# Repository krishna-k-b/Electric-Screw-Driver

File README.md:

# Electric-Screw-Driver
Attempt to make a Torque-sensing DC screwdriver using motor current feedback for real-time torque estimation and inertia aware control

# DRV8701 + RP2040 Brushed DC Screwdriver

Firmware for a handheld brushed-DC screwdriver using a Raspberry Pi Pico (RP2040) and a DRV8701 gate driver in PH/EN mode with an external N-MOSFET H-bridge. Features closed-loop current sensing, configurable torque limiting, soft-start, dithering, and full serial telemetry over CMSIS-DAP / Picoprobe.

## Table of Contents

- [Hardware Overview](#hardware-overview)
- [Pin Map](#pin-map)
- [Current Sensing Circuit](#current-sensing-circuit)
- [Building](#building)
- [Flashing](#flashing)
- [Debug / Serial Interface](#debug--serial-interface)
- [Serial Commands](#serial-commands)
- [State Machine](#state-machine)
- [Torque Control](#torque-control)
- [LED Indicator](#led-indicator)
- [Configuration Reference](#configuration-reference)

---

## Hardware Overview

| Component | Part |
|---|---|
| MCU | Raspberry Pi Pico (RP2040) |
| Gate driver | Texas Instruments DRV8701 |
| Bridge topology | External N-MOSFET H-bridge (PH/EN mode) |
| Current sense | 5 mΩ shunt + DRV8701 SO pin + resistor divider |
| Trigger | Two momentary buttons — CW (GP13) and CCW (GP12) |
| Speed control | Fixed 100 % duty with soft-start ramp (no pot fitted) |

---

## Pin Map

| GPIO | Direction | Function |
|---|---|---|
| GP0 | OUT | UART0 TX → Picoprobe GP5 |
| GP1 | IN | UART0 RX → Picoprobe GP4 |
| GP12 | IN (pull-up) | Button CCW — active LOW |
| GP13 | IN (pull-up) | Button CW — active LOW |
| GP16 | OUT (PWM) | DRV8701 EN/PWM — 20 kHz |
| GP17 | OUT | DRV8701 PH/DIR — HIGH = CW |
| GP18 | OUT | DRV8701 nSLEEP — LOW = Hi-Z |
| GP19 | IN (pull-up) | DRV8701 nFAULT — open-drain active LOW |
| GP26 | AIN | ADC CH0 — SO current sense |
| GP27 | AIN | ADC CH1 — pot (wired, reading disabled) |
| GP25 | OUT | Onboard LED |

---

## Current Sensing Circuit

The DRV8701 SO pin outputs a voltage proportional to motor current. A resistor divider scales it to the RP2040's 3.3 V ADC range.

```
SO pin ──┬── 10 kΩ ──── 3.3 V
         │
         ├── GP26 (ADC CH0)
         │
        20 kΩ
         │
        GND
```

| Parameter | Value |
|---|---|
| Divider ratio (V_ADC / V_SO) | 0.6667 (20 / 30) |
| Amplifier gain | 20 V/V |
| Sense resistor | 5 mΩ |
| SO offset voltage | 50 mV |

**Current calculation** (per loop tick):

```
V_SO_real      = V_ADC / 0.6667
V_SO_on_phase  = V_SO_real / duty_fraction      ← duty-cycle compensation
V_across_amp   = V_SO_on_phase − 0.050 V
I              = V_across_amp / (20 × 0.005)
```

Readings are frozen when duty < 10 % to avoid noise during near-zero on-time. A first-order IIR filter (α = 0.25) smooths the result.

---

## Building

### Prerequisites

- [Raspberry Pi Pico SDK](https://github.com/raspberrypi/pico-sdk) (≥ 1.5)
- CMake ≥ 3.13
- `arm-none-eabi-gcc`

### CMakeLists.txt fragment

```cmake
add_executable(screwdriver DRV_ESD.cpp)

target_link_libraries(screwdriver PRIVATE
    pico_stdlib
    hardware_pwm
    hardware_adc
    hardware_gpio
    hardware_uart
    hardware_watchdog
    hardware_clocks
)

pico_enable_stdio_uart(screwdriver 1)
pico_enable_stdio_usb(screwdriver 0)
pico_add_extra_outputs(screwdriver)
```

### Build

```bash
mkdir build && cd build
cmake ..
make -j4
```

This produces `DRV_ESD.uf2`.

---

## Flashing

Hold the **BOOTSEL** button on the Pico while plugging in USB. Drag `DRV_ESD.uf2` onto the `RPI-RP2` mass-storage device that appears. The board resets and starts running immediately.
Above is for flashing without debugger, i usually flash the .elf file through debugger. Read Pico Debug documentation should you wish to flash using a debugger.

---

## Debug / Serial Interface

Connect a second Pico running [Picoprobe](https://github.com/raspberrypi/picoprobe) firmware:

| Target | Picoprobe |
|---|---|
| GP0 (TX) | GP5 |
| GP1 (RX) | GP4 |
| GND | GND |

Open the CDC serial port at **921 600 baud, 8N1**. All log lines are prefixed with a millisecond timestamp:

```
[T+   1234 ms] STATE  IDLE -> STARTING  [trigger engaged]
[T+   1284 ms] TELEM  STARTING  dir=CW   I= 0.12A ...
```

---

## Serial Commands

Send commands surrounded by angle brackets, e.g. `<help>`.

| Command | Description |
|---|---|
| `<help>` | Full status dump + command list |
| `<status>` | Same as `<help>` |
| `<cw>` | Start motor CW (latched until `<stop>` or torque trip) |
| `<ccw>` | Start motor CCW (latched until `<stop>` or torque trip) |
| `<stop>` | Clear any serial motor request |
| `<ith X.X>` | Set current threshold in amps, e.g. `<ith 4.5>` |

Serial requests behave identically to physical button presses. `<cw>` and `<ccw>` are only accepted from **IDLE** or **STOPPED**; they are ignored and logged otherwise.

---

## State Machine

```
         ┌──────────────────────────────────────────────────────────────────┐
         │  nFAULT asserted (any time)                                      ▼
  BOOT ──► IDLE ──trigger──► STARTING ──ramp done──► RUNNING               FAULT
           ▲                    │                      │  │                   │
           │              early release             trip │  I > 80% Ith       │ nFAULT clear
           │                    │                        ▼  ▼              + holdoff
           │                    └───────────────► STOPPING ◄── DITHERING      │
           │                                          │             │          │
           │                                    cooldown done       │ I < 60% Ith
           │                                          ▼             │
           └──────────────── trigger released ── STOPPED            └──► RUNNING
```

| State | Description |
|---|---|
| `BOOT` | One-shot init, transitions immediately to `IDLE` |
| `IDLE` | Waiting for trigger; bridge is in sleep / Hi-Z |
| `STARTING` | 200 ms linear duty ramp from 0 → 100 % |
| `RUNNING` | Full duty, monitoring current |
| `DITHERING` | Near threshold — duty modulated to hold current just below limit |
| `STOPPING` | EN = 0 (brake), 300 ms cooldown before sleep |
| `STOPPED` | Bridge asleep; waiting for trigger release before next run |
| `FAULT` | nFAULT asserted by DRV8701; motor braked, LED solid ON |

**Trigger logic** — either the physical button *or* a latched serial request counts as a trigger. If both CW and CCW are simultaneously active (buttons or serial), no motion occurs until the conflict resolves.

---

## Torque Control

Three layered mechanisms protect the motor and workpiece:

### 1. Threshold current trip (sustained overcurrent)

The firmware trips if `I_filtered ≥ I_threshold` persists for **5 consecutive milliseconds**. Default threshold is **5.0 A**; adjustable at runtime with `<ith X.X>` (range 2–10 A). On trip, the motor brakes and the state machine enters `STOPPING`.

### 2. Hard limit

If filtered current reaches **14 A** at any time — including during soft-start — the motor brakes immediately regardless of threshold setting. This protects the FETs from thermal runaway.

### 3. Rapid dI/dt (stall detection)

A ring buffer of the last 8 current samples is compared oldest-to-newest. If the window rise exceeds **4 A**, the motor trips. This catches stalls that happen before sustained overcurrent would fire.

### Dithering (soft current limiting)

Between **80 %** and **100 %** of the threshold current the firmware enters `DITHERING` and scales the duty cycle proportionally down to a minimum of **30 %**, holding torque steady rather than hard-tripping. The motor returns to `RUNNING` if current drops back below **60 %** of threshold.

---

## LED Indicator

| LED state | Meaning |
|---|---|
| Off | Idle / stopped / boot |
| Blinking (0.5 s period) | Motor energised (STARTING, RUNNING, DITHERING) |
| Solid ON | FAULT |

---

## Configuration Reference

All compile-time tunables are `constexpr` near the top of `DRV_ESD.cpp`.

| Symbol | Default | Description |
|---|---|---|
| `I_THRESHOLD_DEFAULT_A` | 5.0 A | Starting current threshold (no pot) |
| `I_THRESHOLD_MIN_A` | 2.0 A | Lower bound for `<ith>` command |
| `I_THRESHOLD_MAX_A` | 10.0 A | Upper bound for `<ith>` command |
| `I_HARD_LIMIT_A` | 14.0 A | Unconditional FET protection limit |
| `SOFT_START_MS` | 200 ms | Duty ramp duration on trigger press |
| `COOLDOWN_MS` | 300 ms | Brake hold time before bridge sleeps |
| `FAULT_HOLDOFF_MS` | 150 ms | Debounce after nFAULT clears |
| `OVERCURRENT_CONFIRM_MS` | 5 ms | Sustained OC window before trip |
| `DI_DT_TRIP_A_PER_WIN` | 4.0 A | dI/dt trip threshold over 8-sample window |
| `DITHER_START_FRAC` | 0.80 | Dither zone entry — fraction of I_threshold |
| `DITHER_MIN_DUTY_FRAC` | 0.30 | Minimum PWM duty while dithering |
| `IIR_ALPHA` | 0.25 | Current filter coefficient (higher = faster) |
| `PWM_WRAP` | 6249 | PWM counter wrap → 20 kHz at 125 MHz |
| `LOOP_PERIOD_US` | 5000 µs | Main loop period (200 Hz) |
| `WATCHDOG_TIMEOUT_MS` | 250 ms | Watchdog reset if loop stalls |
| `UART_BAUD` | 921 600 | Debug UART baud rate |

---

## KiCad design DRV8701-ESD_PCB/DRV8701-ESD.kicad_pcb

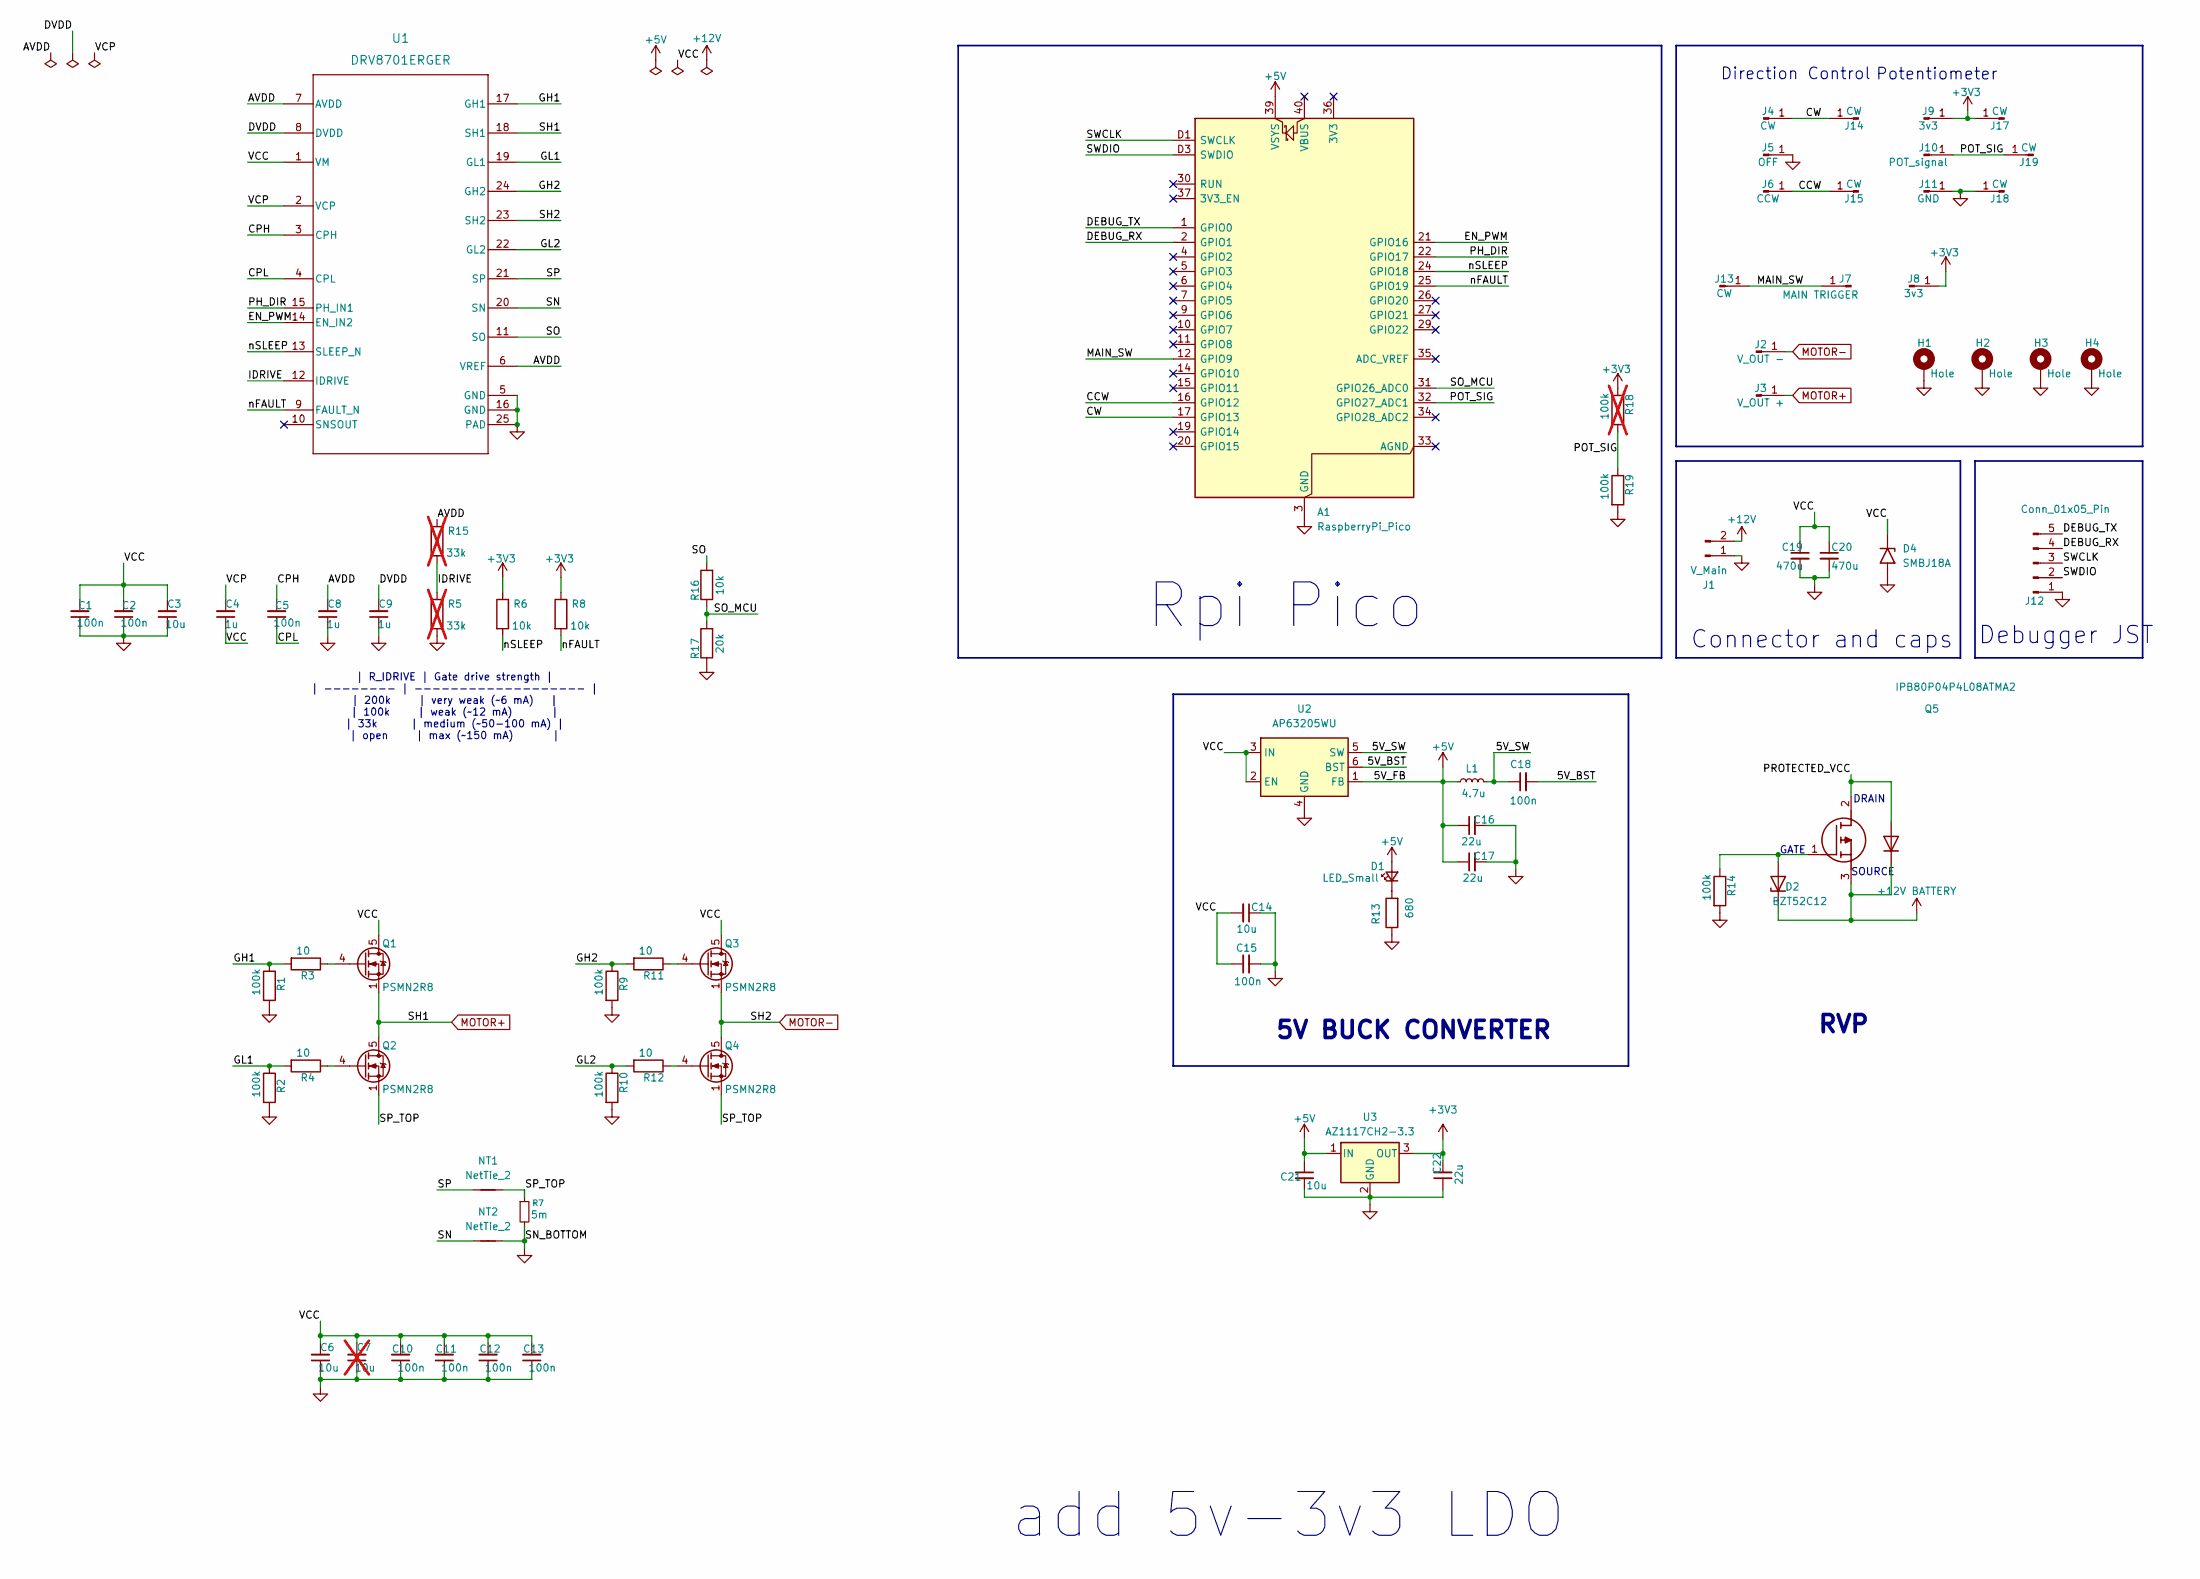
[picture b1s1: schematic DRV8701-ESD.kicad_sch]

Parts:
A1: RaspberryPi_Pico; RaspberryPi_Pico_SMD_HandSolder
C1, C2, C5, C10, C11, C12, C13, C15, C18: 100n; C_0603_1608Metric_Pad1.08x0.95mm_HandSolder
C3, C6, C14, C21: 10u; C_1206_3216Metric_Pad1.33x1.80mm_HandSolder; LCSC C77096
C4, C8, C9: 1u; C_0805_2012Metric_Pad1.18x1.45mm_HandSolder
C7: 10u; C_1206_3216Metric_Pad1.33x1.80mm_HandSolder; LCSC C77096; not fitted
C16, C17, C22: 22u; C_1210_3225Metric_Pad1.33x2.70mm_HandSolder; LCSC C86816
C19, C20: 470u; C_Radial_D10.0mm_H20.0mm_P5.00mm
D1: LED_Small; LED_0603_1608Metric_Pad1.05x0.95mm_HandSolder
D2: BZT52C12; D_SOD-123F
D4: SMBJ18A; D_SMA-SMB_Universal_Handsoldering
H1, H2, H3, H4: Hole; MountingHole_3.2mm_M3_Pad
J1: V_Main; AMASS_XT60-F_1x02_P7.20mm_Vertical
J2: V_OUT -; Solder_Pad_10x10mm_withVias
J3: V_OUT +; Solder_Pad_10x10mm_withVias
J4: CW; PinHeader_1x01_P2.54mm_Vertical
J5: OFF; PinHeader_1x01_P2.54mm_Vertical
J6: CCW; PinHeader_1x01_P2.54mm_Vertical
J7: MAIN TRIGGER; PinHeader_1x01_P2.54mm_Vertical
J8, J9: 3v3; PinHeader_1x01_P2.54mm_Vertical
J10: POT_signal; PinHeader_1x01_P2.54mm_Vertical
J11: GND; PinHeader_1x01_P2.54mm_Vertical
J12: Conn_01x05_Pin; Molex_PicoBlade_53047-0510_1x05_P1.25mm_Vertical
J13, J14, J15, J17, J18, J19: CW; 3.5x3.5_Solder_Pads
L1: 4.7u; L_SMD_6mmx6mm
NT1, NT2: NetTie_2; NetTie-2_SMD_Pad0.2mm
Q1, Q2, Q3, Q4: PSMN2R8; LFPAK56
Q5: IPB80P04P4L08ATMA2; TO-263-2
R1, R2, R9, R10, R14, R19: 100k; R_0603_1608Metric_Pad0.98x0.95mm_HandSolder
R3, R4, R11, R12: 10; R_0603_1608Metric_Pad0.98x0.95mm_HandSolder
R5, R15: 33k; R_0603_1608Metric_Pad0.98x0.95mm_HandSolder; not fitted
R6, R8, R16: 10k; R_0603_1608Metric_Pad0.98x0.95mm_HandSolder
R7: 5m; R_2512_6332Metric_Pad1.40x3.35mm_HandSolder
R13: 680; C_0603_1608Metric_Pad1.08x0.95mm_HandSolder
R17: 20k; R_0603_1608Metric_Pad0.98x0.95mm_HandSolder
R18: 100k; R_0603_1608Metric_Pad0.98x0.95mm_HandSolder; not fitted
U1: DRV8701ERGER; RGE0024F_NV
U2: AP63205WU; TSOT-23-6
U3: AZ1117CH2-3.3; SOT-223-3_TabPin2

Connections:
+3V3: C22.2, J8.1, J9.1, J17.1, R6.1, R8.1, R18.1, U3.3 (OUT)
+5V: A1.39 (VSYS), C16.1, C17.1, C21.1, D1.2 (A), L1.1, U2.1 (FB), U3.1 (IN)
/5V_BST: C18.2, U2.6 (BST)
/5V_SW: C18.1, L1.2, U2.5 (SW)
/AVDD: C8.2, R15.1, U1.6 (VREF), U1.7 (AVDD)
/CCW: A1.16 (GPIO12), J6.1, J15.1
/CPH: C5.2, U1.3 (CPH)
/CPL: C5.1, U1.4 (CPL)
/CW: A1.17 (GPIO13), J4.1, J14.1
/DEBUG_RX: A1.2 (GPIO1), J12.4
/DEBUG_TX: A1.1 (GPIO0), J12.5
/DVDD: C9.2, U1.8 (DVDD)
/EN_PWM: A1.21 (GPIO16), U1.14 (EN_IN2)
/GH1: R1.1, R3.2, U1.17 (GH1)
/GH2: R9.1, R11.2, U1.24 (GH2)
/GL1: R2.1, R4.2, U1.19 (GL1)
/GL2: R10.1, R12.2, U1.22 (GL2)
/IDRIVE: R5.1, R15.2, U1.12 (IDRIVE)
/MAIN_SW: A1.12 (GPIO9), J7.1, J13.1
/PH_DIR: A1.22 (GPIO17), U1.15 (PH_IN1)
/POT_SIG: A1.32 (GPIO27_ADC1), J10.1, J19.1, R18.2, R19.1
/SN: NT2.1, U1.20 (SN)
/SO: R16.2, U1.11 (SO)
/SO_MCU: A1.31 (GPIO26_ADC0), R16.1, R17.2
/SP: NT1.1, U1.21 (SP)
/SP_TOP: NT1.2, Q2.1 (S), Q2.2 (S), Q2.3 (S), Q4.1 (S), Q4.2 (S), Q4.3 (S), R7.1
/SWCLK: A1.D1 (SWCLK), J12.3
/SWDIO: A1.D3 (SWDIO), J12.2
/VCP: C4.2, U1.2 (VCP)
/nFAULT: A1.25 (GPIO19), R8.2, U1.9 (FAULT_N)
/nSLEEP: A1.24 (GPIO18), R6.2, U1.13 (SLEEP_N)
GND: A1.3 (GND), A1.8 (GND), A1.13 (GND), A1.18 (GND), A1.23 (GND), A1.28 (GND), A1.38 (GND), A1.D2 (GND), C1.1, C2.1, C3.1, C6.1, C7.1, C8.1, C9.1, C10.1, C11.1, C12.1, C13.1, C14.1, C15.2, C16.2, C17.2, C19.2, C20.2, C21.2, C22.1, D4.2 (A2), H1.1, H2.1, H3.1, H4.1, J1.1, J5.1, J11.1, J12.1, J18.1, NT2.2, R1.2, R2.2, R5.2, R7.2, R9.2, R10.2, R13.1, R14.2, R17.1, R19.2, U1.5 (GND), U1.16 (GND), U1.25 (PAD), U2.4 (GND), U3.2 (GND)
MOTOR+: J3.1, Q1.1 (S), Q1.2 (S), Q1.3 (S), Q2.5 (D), U1.18 (SH1)
MOTOR-: J2.1, Q3.1 (S), Q3.2 (S), Q3.3 (S), Q4.5 (D), U1.23 (SH2)
unnamed: D1.1 (K), R13.2
unnamed: D2.2 (A), Q5.1 (G), R14.1
unnamed: Q1.4 (G), R3.1
unnamed: Q2.4 (G), R4.1
unnamed: Q3.4 (G), R11.1
unnamed: Q4.4 (G), R12.1

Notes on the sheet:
Potentiometer
5V BUCK CONVERTER
Debugger JST
DRAIN
Direction Control
GATE
| R_IDRIVE | Gate drive strength | | -------- | ------------------- | | 200k | very weak (~6 mA) | | 100k | weak (~12 mA) | | 33k | medium (~50-100 mA) | | open | max (~150 mA) |
SOURCE
add 5v-3v3 LDO
Rpi Pico
RVP
Connector and caps

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
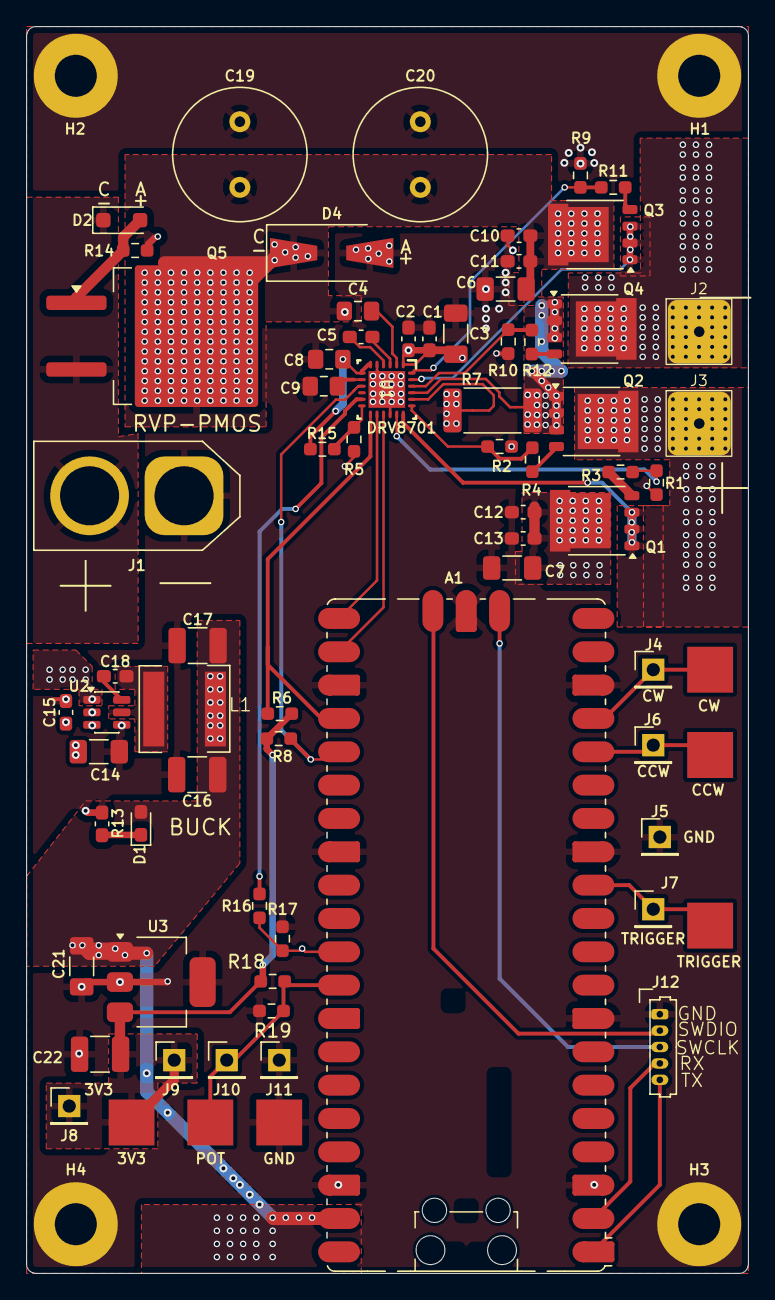
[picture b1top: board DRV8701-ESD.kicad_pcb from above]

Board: 4 copper layers, 55.0 x 95.0 mm, 78 parts (0 on the bottom side), 42 nets.

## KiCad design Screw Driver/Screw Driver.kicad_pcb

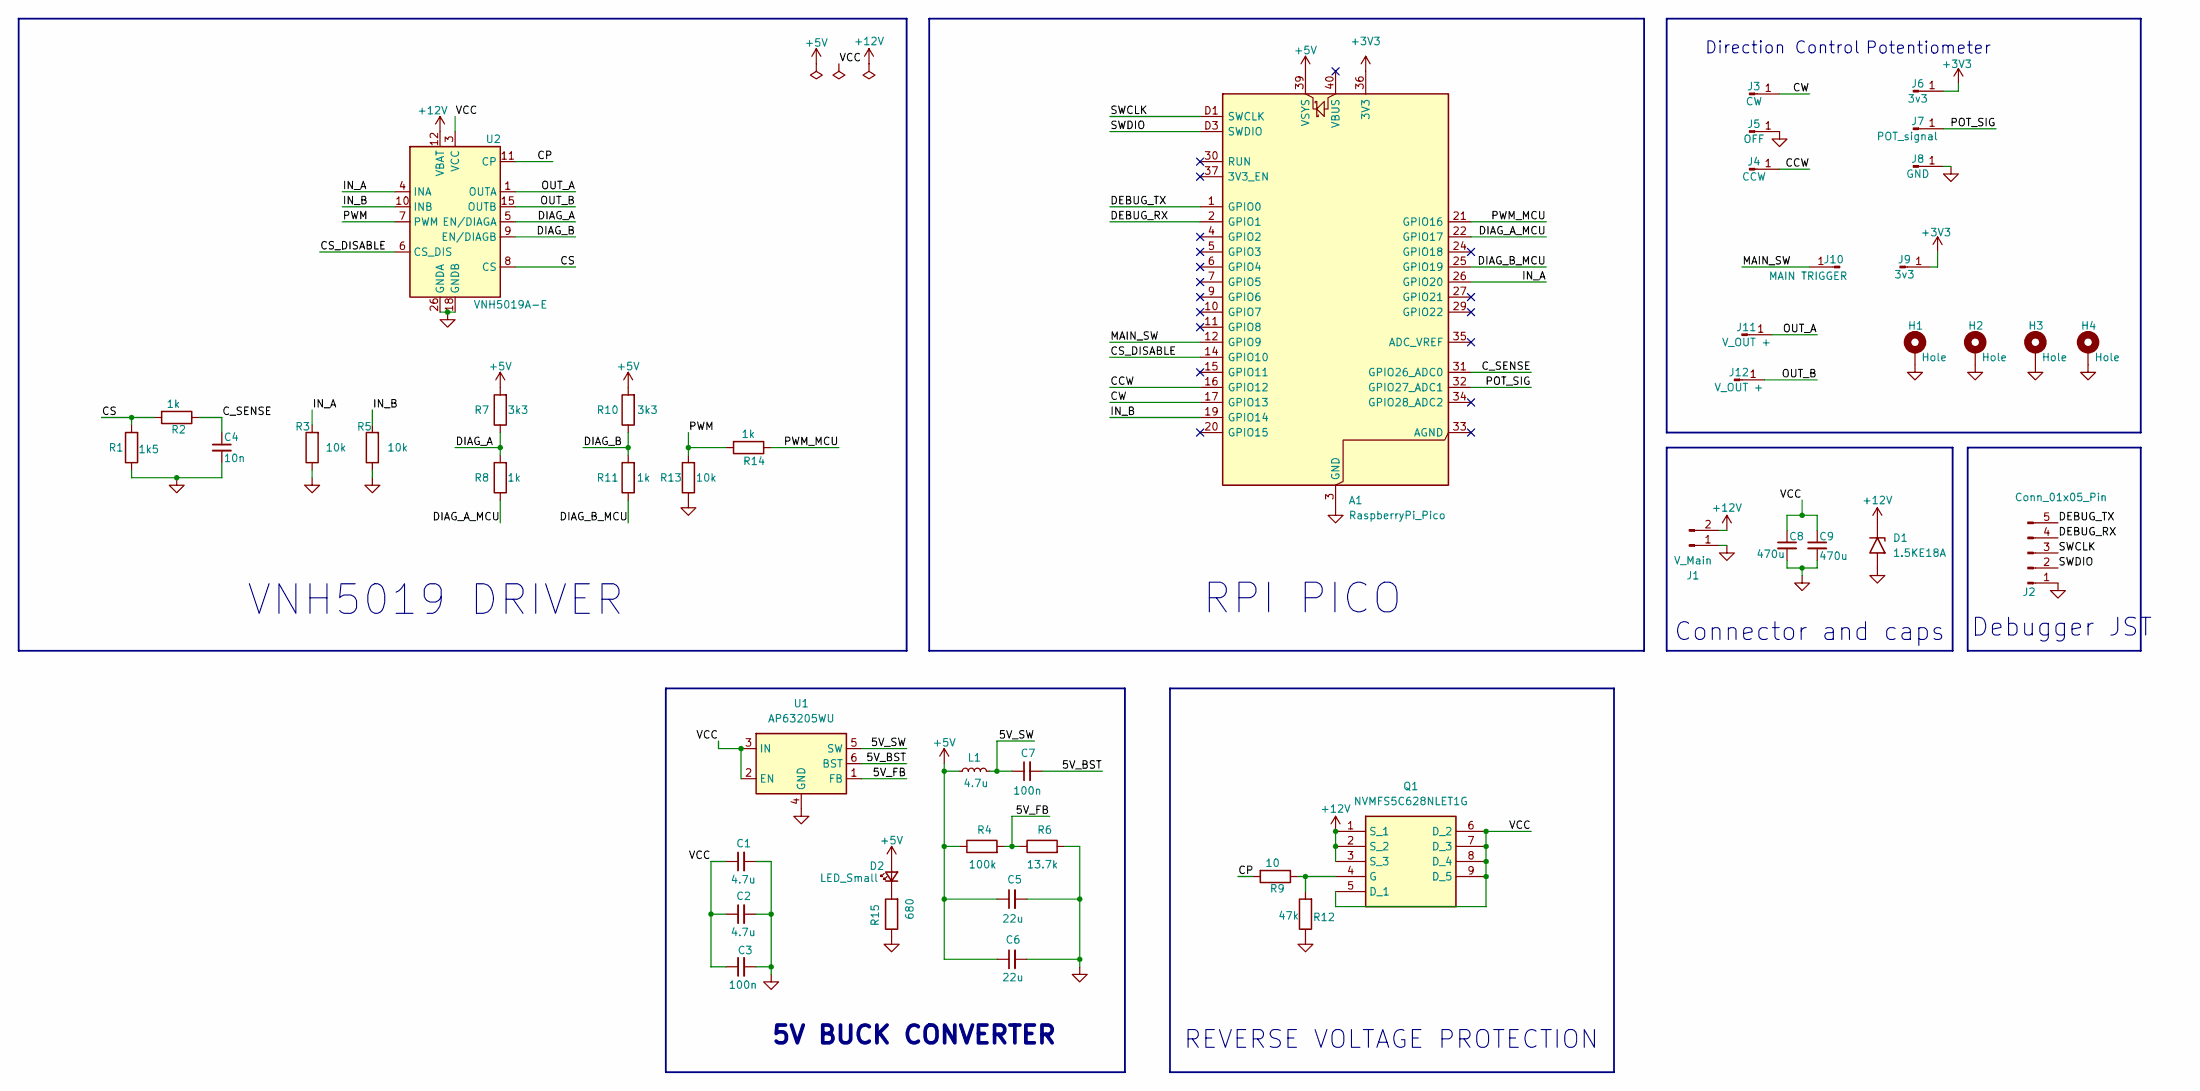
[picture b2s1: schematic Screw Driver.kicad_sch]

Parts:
A1: RaspberryPi_Pico; RaspberryPi_Pico_SMD_HandSolder
C1, C2: 4.7u; C_1206_3216Metric_Pad1.33x1.80mm_HandSolder; LCSC C77096
C3, C7: 100n; C_0603_1608Metric_Pad1.08x0.95mm_HandSolder
C4: 10n; C_0603_1608Metric_Pad1.08x0.95mm_HandSolder
C5, C6: 22u; C_0805_2012Metric_Pad1.18x1.45mm_HandSolder; LCSC C86816
C8, C9: 470u; C_Radial_D10.0mm_H20.0mm_P5.00mm
D1: 1.5KE18A; D_DO-201AE_P15.24mm_Horizontal
D2: LED_Small; LED_0603_1608Metric_Pad1.05x0.95mm_HandSolder
H1, H2, H3, H4: Hole; MountingHole_3.2mm_M3_Pad
J1: V_Main; AMASS_XT60-F_1x02_P7.20mm_Vertical
J2: Conn_01x05_Pin; Molex_PicoBlade_53047-0510_1x05_P1.25mm_Vertical
J3: CW; PinHeader_1x01_P2.54mm_Vertical
J4: CCW; PinHeader_1x01_P2.54mm_Vertical
J5: OFF; PinHeader_1x01_P2.54mm_Vertical
J6, J9: 3v3; PinHeader_1x01_P2.54mm_Vertical
J7: POT_signal; PinHeader_1x01_P2.54mm_Vertical
J8: GND; PinHeader_1x01_P2.54mm_Vertical
J10: MAIN TRIGGER; PinHeader_1x01_P2.54mm_Vertical
J11, J12: V_OUT +; Solder_Pad_10x10mm_withVias
L1: 4.7u; L_Changjiang_FXL0420
Q1: NVMFS5C628NLET1G; ONSemi_SO-8FL_488AA
R1: 1k5; R_0603_1608Metric_Pad0.98x0.95mm_HandSolder
R2, R8, R11, R14: 1k; R_0603_1608Metric_Pad0.98x0.95mm_HandSolder
R3, R5, R13: 10k; R_0603_1608Metric_Pad0.98x0.95mm_HandSolder
R4: 100k; R_0603_1608Metric_Pad0.98x0.95mm_HandSolder
R6: 13.7k; C_0603_1608Metric_Pad1.08x0.95mm_HandSolder
R7, R10: 3k3; R_0603_1608Metric_Pad0.98x0.95mm_HandSolder
R9: 10; R_0603_1608Metric_Pad0.98x0.95mm_HandSolder
R12: 47k; R_0603_1608Metric_Pad0.98x0.95mm_HandSolder
R15: 680; C_0603_1608Metric_Pad1.08x0.95mm_HandSolder
U1: AP63205WU; TSOT-23-6
U2: VNH5019A-E; ST_MultiPowerSO-30

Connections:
+3V3: A1.36 (3V3), J6.1, J9.1
+5V: A1.39 (VSYS), C5.1, C6.1, D2.2 (A), L1.1, R4.1, R7.2, R10.2
+12V: D1.1 (A1), J1.2, Q1.1 (S_1), Q1.2 (S_2), Q1.3 (S_3), U2.12 (VBAT)
/5V_BST: C7.2, U1.6 (BST)
/5V_FB: R4.2, R6.1, U1.1 (FB)
/5V_SW: C7.1, L1.2, U1.5 (SW)
/CCW: A1.16 (GPIO12), J4.1
/CP: R9.2, U2.11 (CP)
/CS: R1.2, R2.2, U2.8 (CS)
/CS_DISABLE: A1.14 (GPIO10), U2.6 (CS_DIS)
/CW: A1.17 (GPIO13), J3.1
/C_SENSE: A1.31 (GPIO26_ADC0), C4.1, R2.1
/DEBUG_RX: A1.2 (GPIO1), J2.4
/DEBUG_TX: A1.1 (GPIO0), J2.5
/DIAG_A: R7.1, R8.2, U2.5 (EN/DIAGA)
/DIAG_A_MCU: A1.22 (GPIO17), R8.1
/DIAG_B: R10.1, R11.2, U2.9 (EN/DIAGB)
/DIAG_B_MCU: A1.25 (GPIO19), R11.1
/IN_A: A1.26 (GPIO20), R3.2, U2.4 (INA)
/IN_B: A1.19 (GPIO14), R5.2, U2.10 (INB)
/MAIN_SW: A1.12 (GPIO9), J10.1
/OUT_A: J11.1, U2.1 (OUTA), U2.25 (OUTA), U2.30 (OUTA), U2.33 (OUTA)
/OUT_B: J12.1, U2.15 (OUTB), U2.16 (OUTB), U2.21 (OUTB), U2.32 (OUTB)
/POT_SIG: A1.32 (GPIO27_ADC1), J7.1
/PWM: R13.2, R14.2, U2.7 (PWM)
/PWM_MCU: A1.21 (GPIO16), R14.1
/SWCLK: A1.D1 (SWCLK), J2.3
/SWDIO: A1.D3 (SWDIO), J2.2
/VCC: C1.1, C2.1, C3.1, C8.1, C9.1, Q1.5 (D_1), Q1.6 (D_2), Q1.7 (D_3), Q1.8 (D_4), Q1.9 (D_5), U1.2 (EN), U1.3 (IN), U2.3 (VCC), U2.13 (VCC), U2.23 (VCC), U2.31 (VCC)
GND: A1.3 (GND), A1.8 (GND), A1.13 (GND), A1.18 (GND), A1.23 (GND), A1.28 (GND), A1.38 (GND), A1.D2 (GND), C1.2, C2.2, C3.2, C4.2, C5.2, C6.2, C8.2, C9.2, D1.2 (A2), H1.1, H2.1, H3.1, H4.1, J1.1, J2.1, J5.1, J8.1, R1.1, R3.1, R5.1, R6.2, R12.1, R13.1, R15.1, U1.4 (GND), U2.18 (GNDB), U2.19 (GNDB), U2.20 (GNDB), U2.26 (GNDA), U2.27 (GNDA), U2.28 (GNDA)
unnamed: D2.1 (K), R15.2
unnamed: Q1.4 (G), R9.1, R12.2

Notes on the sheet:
Direction Control
Connector and caps
5V BUCK CONVERTER
VNH5019 DRIVER
REVERSE VOLTAGE PROTECTION
Potentiometer
Debugger JST
RPI PICO

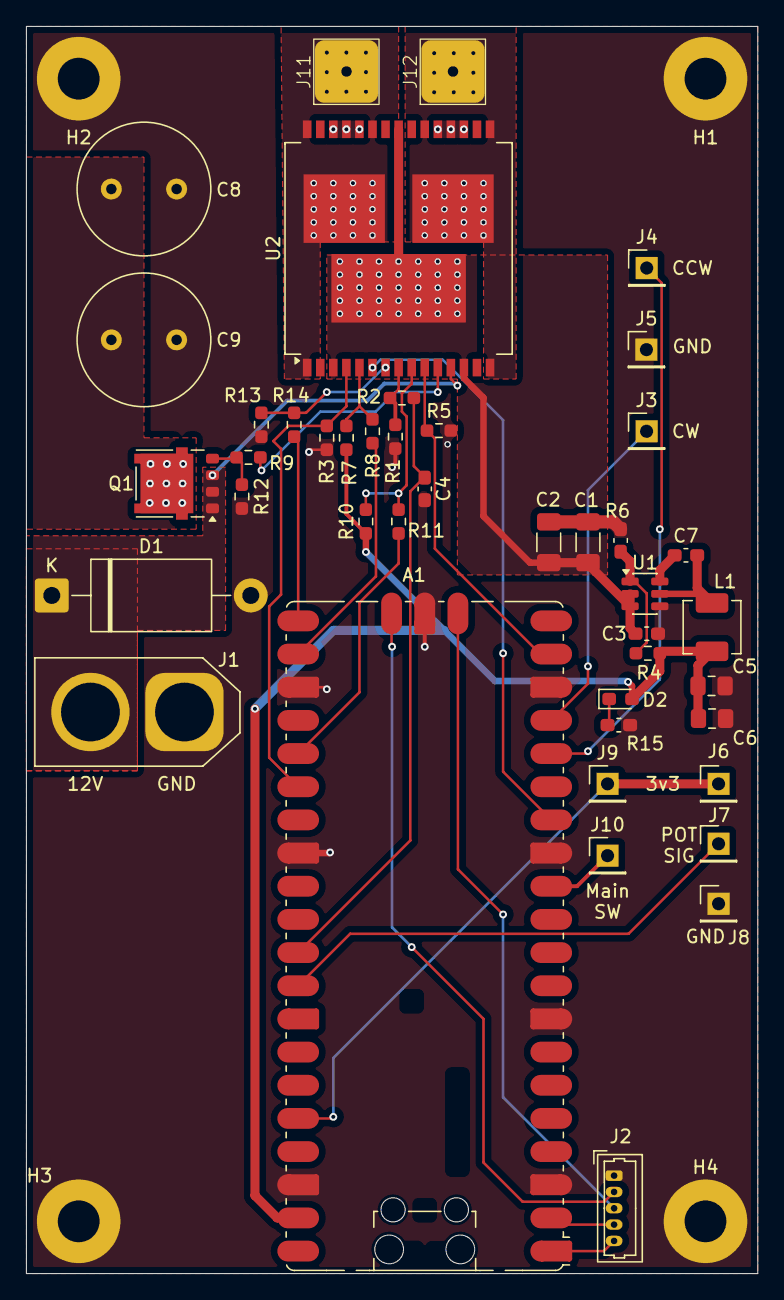
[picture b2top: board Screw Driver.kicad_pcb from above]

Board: 2 copper layers, 56.0 x 95.5 mm, 47 parts (0 on the bottom side), 32 nets.

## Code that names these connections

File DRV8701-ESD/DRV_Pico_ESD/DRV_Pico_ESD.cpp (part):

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/* ---- Pin map ---- */
static constexpr uint PIN_UART_TX   = 0;
static constexpr uint PIN_UART_RX   = 1;
static constexpr uint PIN_MAIN_SW   = 9;
static constexpr uint PIN_BTN_CCW   = 12;
static constexpr uint PIN_BTN_CW    = 13;
static constexpr uint PIN_EN_PWM    = 16;
static constexpr uint PIN_PH_DIR    = 17;
static constexpr uint PIN_NSLEEP    = 18;
static constexpr uint PIN_NFAULT    = 19;
static constexpr uint PIN_ADC_SO    = 26;
static constexpr uint PIN_ADC_POT   = 27;
static constexpr uint ADC_CH_SO     = 0;
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static constexpr int      OVERCURRENT_CONFIRM_MS = 5;       // dwell at I>Ith before trip

/* ---- UART ---- */
static constexpr uint     UART_ID_NUM         = 0;          // uart0 on GPIO0/1
static constexpr uint32_t UART_BAUD           = 115200;
#define UART_ID  uart0

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
enum class Direction : uint8_t {
    CW = 1,         // PH = HIGH
    CCW = 0         // PH = LOW
};

struct Button {
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static void gpio_init_all(void)
{
    /* All control GPIOs: configure to safe state BEFORE enabling outputs.
       During brown-out / re-boot, the DRV8701 sees pulldowns + nSLEEP=0,
       which puts the bridge into Hi-Z. */

    /* nSLEEP -- output, force low (sleep) until we are ready */
    gpio_init(PIN_NSLEEP);
    gpio_put(PIN_NSLEEP, 0);
    gpio_set_dir(PIN_NSLEEP, GPIO_OUT);

    /* PH -- output, default CW (HIGH) */
    gpio_init(PIN_PH_DIR);
    gpio_put(PIN_PH_DIR, 1);
    gpio_set_dir(PIN_PH_DIR, GPIO_OUT);

    /* nFAULT -- input with pull-up (external 10k recommended) */
    gpio_init(PIN_NFAULT);
    gpio_set_dir(PIN_NFAULT, GPIO_IN);
    gpio_pull_up(PIN_NFAULT);

    /* Buttons -- input, pull-up, active LOW */
    const uint btns[] = {PIN_MAIN_SW, PIN_BTN_CW, PIN_BTN_CCW};
    for (uint p : btns) {
        gpio_init(p);
        gpio_set_dir(p, GPIO_IN);
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
static void pwm_init_motor(void)
{
    gpio_set_function(PIN_EN_PWM, GPIO_FUNC_PWM);
    g.pwm_slice = pwm_gpio_to_slice_num(PIN_EN_PWM);
    g.pwm_chan  = pwm_gpio_to_channel(PIN_EN_PWM);

    pwm_config cfg = pwm_get_default_config();
    pwm_config_set_wrap(&cfg, PWM_WRAP);
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static void motor_set_direction(Direction d)
{
    g.dir = d;
    gpio_put(PIN_PH_DIR, d == Direction::CW ? 1 : 0);
}

static void motor_brake(void)
{
    /* nSLEEP=1, EN=0 -> low-side slow decay = brake (Table 1, datasheet). */
    motor_set_duty(0);
    gpio_put(PIN_NSLEEP, 1);
}

static void motor_sleep(void)
{
    motor_set_duty(0);
    gpio_put(PIN_NSLEEP, 0);
}

static void motor_wake(void)
{
    motor_set_duty(0);
    gpio_put(PIN_NSLEEP, 1);
    sleep_ms(WAKE_DELAY_MS);  // only at state transition; not in hot loop
}

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    }

    /* nFAULT is open-drain, active LOW. */
    g.nfault_asserted = (gpio_get(PIN_NFAULT) == 0);

    /* Analog */
    g.so_v  = adc_to_volts(adc_read_channel(ADC_CH_SO));
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    printf("sys_clk = %u Hz\n", clock_get_hz(clk_sys));
    printf("PWM = 20 kHz, wrap=%u, clkdiv=%.2f\n", PWM_WRAP, (double)PWM_CLKDIV);

    /* --- 2. GPIOs into safe state (nSLEEP=0) --- */
    gpio_init_all();

    /* --- 3. Peripherals --- */
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    g.state         = State::BOOT;
    g.dir           = Direction::CW;
    g.pending_dir   = Direction::CW;
    g.pwm_slice     = pwm_gpio_to_slice_num(PIN_EN_PWM);
    g.pwm_chan      = pwm_gpio_to_channel(PIN_EN_PWM);
    button_init(g.sw_main, PIN_MAIN_SW);
    button_init(g.sw_cw,   PIN_BTN_CW);
    button_init(g.sw_ccw,  PIN_BTN_CCW);
    g.last_log      = get_absolute_time();
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
    /* --- 6. Sanity: confirm nFAULT not stuck low (would be a wiring issue) --- */
    sleep_ms(10);
    if (gpio_get(PIN_NFAULT) == 0) {
        printf("[WARN] nFAULT is asserted at boot. Check pull-up / VM / wiring.\n");
    }

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
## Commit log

2026-03-12 Added essentials, tentative PCB layout
2026-03-17 Some routing done
2026-03-18 Some more routing done
2026-03-22 Routing fully done
2026-04-01 Improved Layout
2026-04-03 Changed Driver
2026-04-03 Made Schematic for DRV
2026-04-04 Finalized few components
2026-04-07 Component Placement - Tentative
2026-04-08 Added PMOS, Changed VREF to 3v3, Added 5->3v3 LDO, Placed components tentatively. Yet to review.
2026-04-08 Some layout changes
2026-04-08 Some more stuff added
2026-04-08 Changes done after review
2026-04-09 Routing Done, yet to review
2026-04-10 Added SMD and THT Debug Connectors. Some small changes.
2026-04-10 Made improvements.
2026-04-11 Added pours, final changes
2026-04-15 Made some final changes, ordered.
2026-04-21 Added Firmware block, yet to start
2026-05-06 Wrote code, need to test
2026-05-06 Wrote code, need to check
2026-05-30 Working COde, final PCB files added.
